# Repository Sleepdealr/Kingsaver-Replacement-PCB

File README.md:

# Kingsaver Replacement PCB

Replacement PCB for the Kingsaver

This has been prototyped and is confirmed working

<br />This work is licensed under a <a rel="license" href="http://creativecommons.org/licenses/by-nc-sa/4.0/">Creative Commons Attribution-NonCommercial-ShareAlike 4.0 Unported License</a>.

# Production

Production gerbers are zipped in the `Gerbers` folder, with JLC assembly files in the `jlcpcb/assembly` folder

You can get USB connectors off LCSC at <https://lcsc.com/product-detail/USB-Connectors_Jing-Extension-of-the-Electronic-Co-920-462A2021D10102_C46398.html>

Photo of proto:

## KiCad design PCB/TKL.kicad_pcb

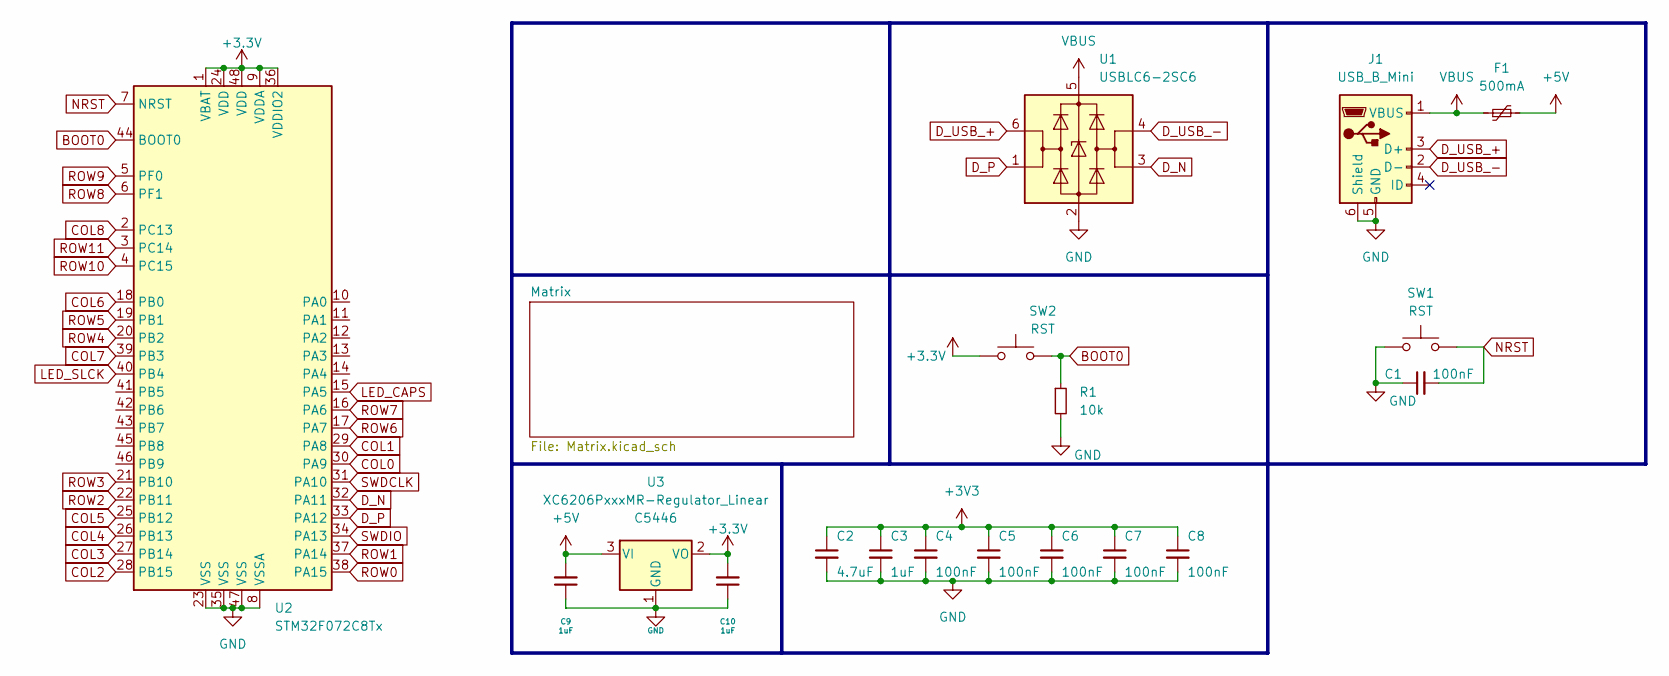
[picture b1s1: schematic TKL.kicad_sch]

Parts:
C1, C4, C5, C6, C7, C8: 100nF; C_0402_1005Metric; LCSC C307331
C2: 4.7uF; C_0402_1005Metric; LCSC C52923
C3, C9, C10: 1uF; C_0402_1005Metric; LCSC C52923
F1: 500mA; Fuse_1206_3216Metric
J1: USB_B_Mini; USB-Mini-B_ LCSC-C46398; LCSC C105424
R1: 10k; R_0402_1005Metric
SW1, SW2: RST; SW_SPST_SKQG_WithoutStem
U1: USBLC6-2SC6; SOT-23-6
U2: STM32F072C8Tx; LQFP-48_7x7mm_P0.5mm
U3: XC6206PxxxMR-Regulator_Linear; SOT-23; LCSC C5446

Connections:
+5V: C9.2, F1.2, U3.3 (VI)
BOOT0: R1.1, SW2.2, U2.44 (BOOT0)
COL0: U2.30 (PA9); also elsewhere on the board
COL1: U2.29 (PA8); also elsewhere on the board
COL2: U2.28 (PB15); also elsewhere on the board
COL3: U2.27 (PB14); also elsewhere on the board
COL4: U2.26 (PB13); also elsewhere on the board
COL5: U2.25 (PB12); also elsewhere on the board
COL6: U2.18 (PB0); also elsewhere on the board
COL7: U2.39 (PB3); also elsewhere on the board
COL8: U2.2 (PC13); also elsewhere on the board
D_N: U1.3 (I/O2), U2.32 (PA11)
D_P: U1.1 (I/O1), U2.33 (PA12)
D_USB_+: J1.3 (D+), U1.6 (I/O1)
D_USB_-: J1.2 (D-), U1.4 (I/O2)
GND: C1.1, C2.2, C3.2, C4.2, C5.2, C6.2, C7.2, C8.2, C9.1, C10.1, J1.5 (GND), J1.6 (Shield), R1.2, SW1.1, U1.2 (GND), U2.8 (VSSA), U2.23 (VSS), U2.35 (VSS), U2.47 (VSS), U3.1 (GND); also elsewhere on the board
LED_CAPS: U2.15 (PA5); also elsewhere on the board
LED_SLCK: U2.40 (PB4); also elsewhere on the board
NRST: C1.2, SW1.2, U2.7 (NRST)
ROW0: U2.38 (PA15); also elsewhere on the board
ROW1: U2.37 (PA14); also elsewhere on the board
ROW2: U2.22 (PB11); also elsewhere on the board
ROW3: U2.21 (PB10); also elsewhere on the board
ROW4: U2.20 (PB2); also elsewhere on the board
ROW5: U2.19 (PB1); also elsewhere on the board
ROW6: U2.17 (PA7); also elsewhere on the board
ROW7: U2.16 (PA6); also elsewhere on the board
ROW8: U2.6 (PF1); also elsewhere on the board
ROW9: U2.5 (PF0); also elsewhere on the board
ROW10: U2.4 (PC15); also elsewhere on the board
ROW11: U2.3 (PC14); also elsewhere on the board
SWDCLK: U2.31 (PA10)
SWDIO: U2.34 (PA13)
VBUS: F1.1, J1.1 (VBUS), U1.5 (VBUS)

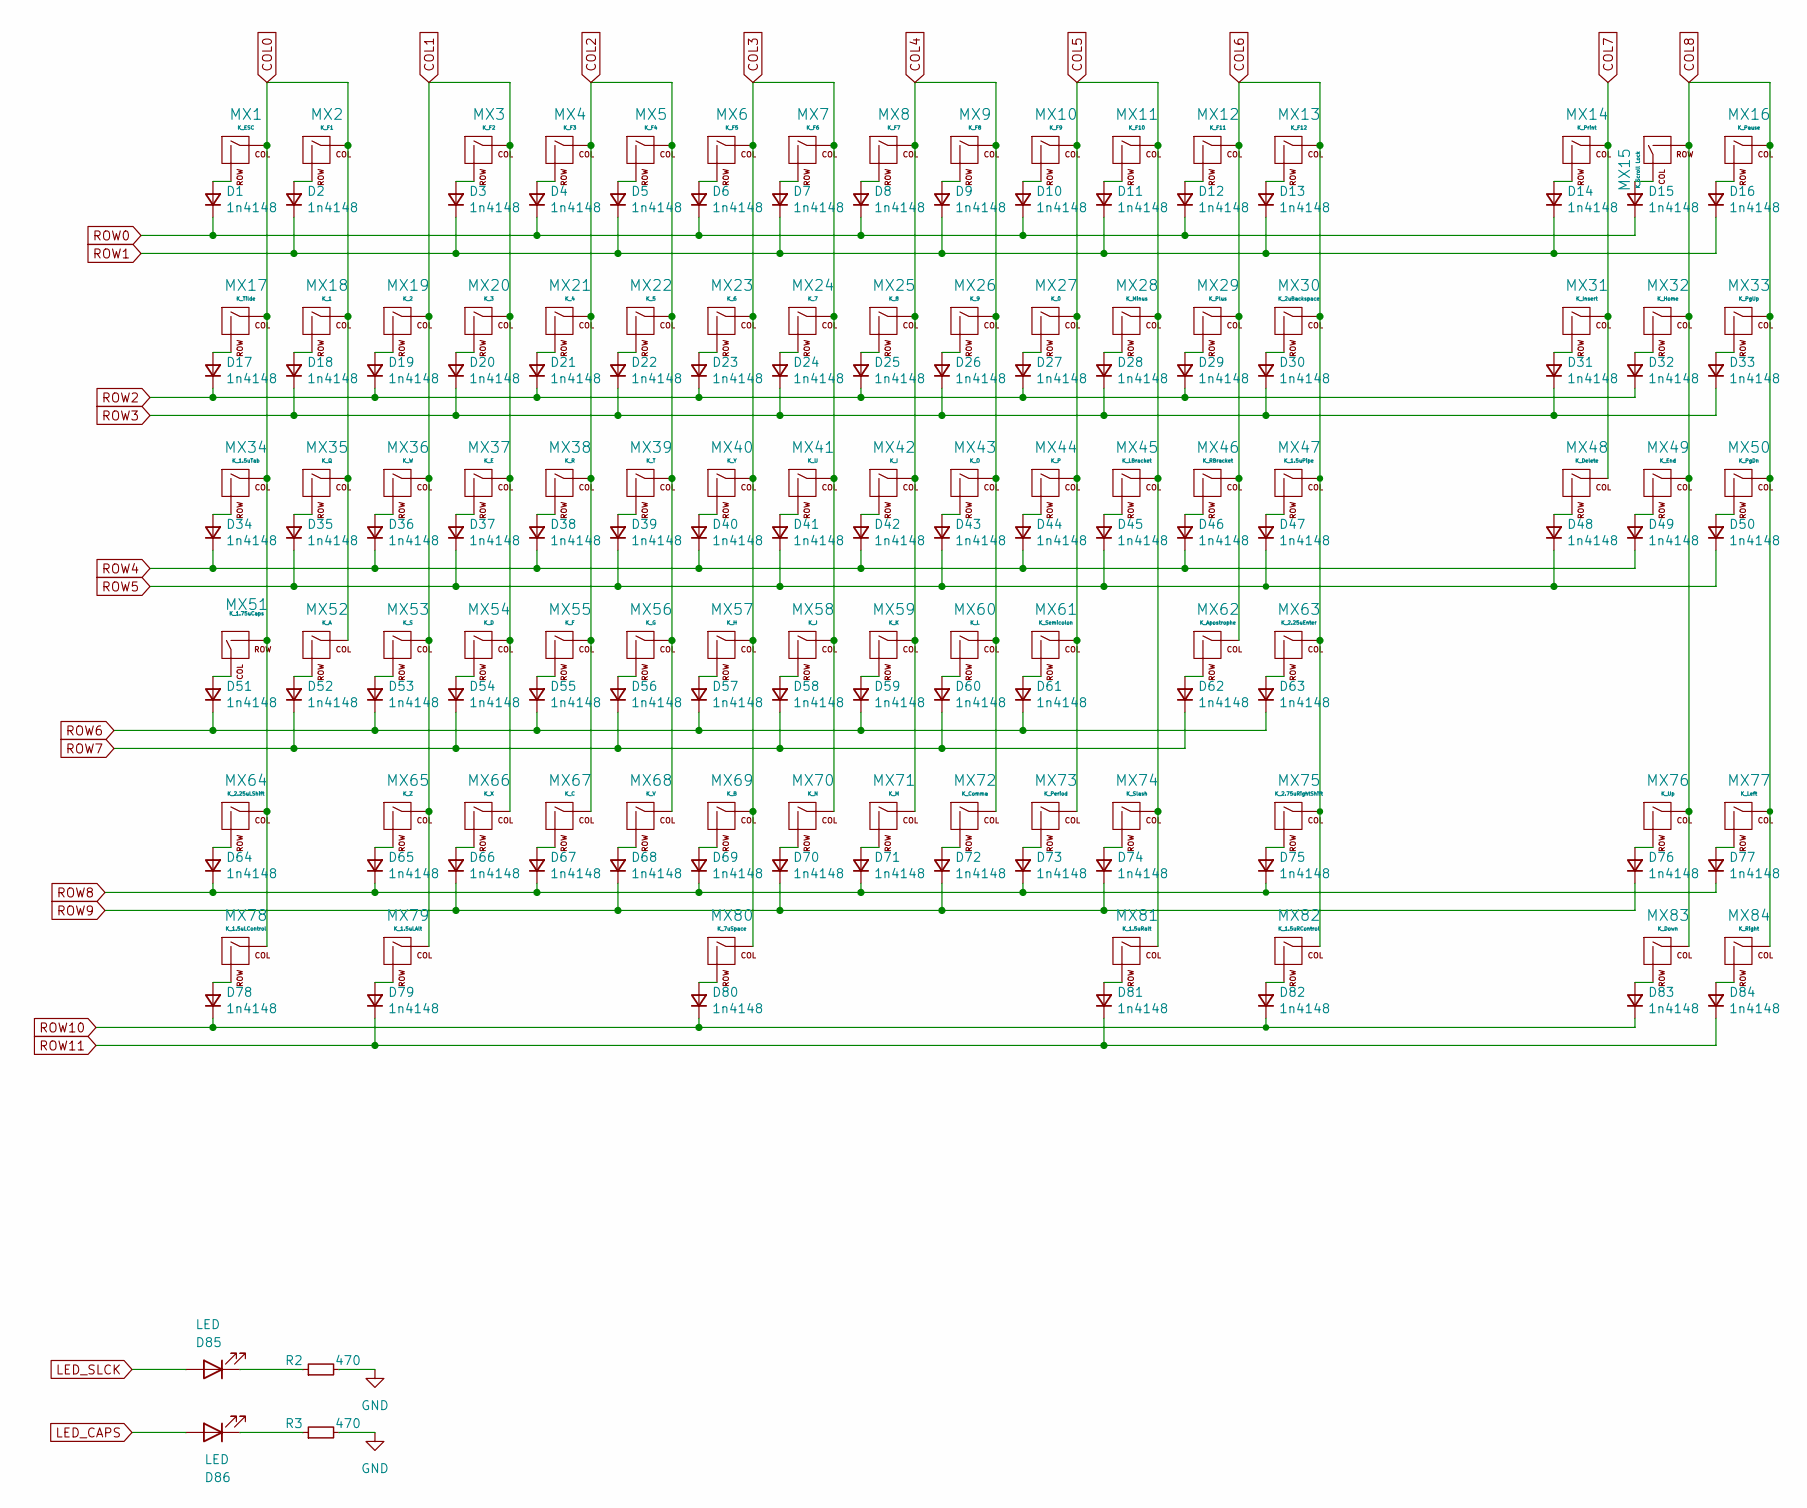
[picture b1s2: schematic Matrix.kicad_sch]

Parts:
D1, D2, D3, D4, D5, D6, D7, D8, D9, D10, D11, D12, D13, D14, D15, D16, D17, D18, D19, D20, D21, D22, D23, D24, D25, D26, D27, D28, D29, D30, D31, D32, D33, D34, D35, D36, D37, D38, D39, D40, D41, D42, D43, D44, D45, D46, D47, D48, D49, D50, D51, D52, D53, D54, D55, D56, D57, D58, D59, D60, D61, D62, D63, D64, D65, D66, D67, D68, D69, D70, D71, D72, D73, D74, D75, D76, D77, D78, D79, D80, D81, D82, D83, D84: 1n4148; D_SOD-123-EditSkilk; LCSC C81598
D85, D86: LED; ALPS-LEDONLY
MX1: K_ESC; SW_Alps_1u
MX2: K_F1; SW_Alps_1u
MX3: K_F2; SW_Alps_1u
MX4: K_F3; SW_Alps_1u
MX5: K_F4; SW_Alps_1u
MX6: K_F5; SW_Alps_1u
MX7: K_F6; SW_Alps_1u
MX8: K_F7; SW_Alps_1u
MX9: K_F8; SW_Alps_1u
MX10: K_F9; SW_Alps_1u
MX11: K_F10; SW_Alps_1u
MX12: K_F11; SW_Alps_1u
MX13: K_F12; SW_Alps_1u
MX14: K_Print; SW_Alps_1u
MX15: K_Scroll Lock; SW_Alps_1u
MX16: K_Pause; SW_Alps_1u
MX17: K_Tilde; SW_Alps_1u
MX18: K_1; SW_Alps_1u
MX19: K_2; SW_Alps_1u
MX20: K_3; SW_Alps_1u
MX21: K_4; SW_Alps_1u
MX22: K_5; SW_Alps_1u
MX23: K_6; SW_Alps_1u
MX24: K_7; SW_Alps_1u
MX25: K_8; SW_Alps_1u
MX26: K_9; SW_Alps_1u
MX27: K_0; SW_Alps_1u
MX28: K_Minus; SW_Alps_1u
MX29: K_Plus; SW_Alps_1u
MX30: K_2uBackspace; SW_Alps_1u
MX31: K_Insert; SW_Alps_1u
MX32: K_Home; SW_Alps_1u
MX33: K_PgUp; SW_Alps_1u
MX34: K_1.5uTab; SW_Alps_1.5u
MX35: K_Q; SW_Alps_1u
MX36: K_W; SW_Alps_1u
MX37: K_E; SW_Alps_1u
MX38: K_R; SW_Alps_1u
MX39: K_T; SW_Alps_1u
MX40: K_Y; SW_Alps_1u
MX41: K_U; SW_Alps_1u
MX42: K_I; SW_Alps_1u
MX43: K_O; SW_Alps_1u
MX44: K_P; SW_Alps_1u
MX45: K_LBracket; SW_Alps_1u
MX46: K_RBracket; SW_Alps_1u
MX47: K_1.5uPipe; SW_Alps_1.75u
MX48: K_Delete; SW_Alps_1u
MX49: K_End; SW_Alps_1u
MX50: K_PgDn; SW_Alps_1u
MX51: K_1.75uCaps; SW_Alps_1.75u
MX52: K_A; SW_Alps_1u
MX53: K_S; SW_Alps_1u
MX54: K_D; SW_Alps_1u
MX55: K_F; SW_Alps_1u
MX56: K_G; SW_Alps_1u
MX57: K_H; SW_Alps_1u
MX58: K_J; SW_Alps_1u
MX59: K_K; SW_Alps_1u
MX60: K_L; SW_Alps_1u
MX61: K_Semicolon; SW_Alps_1u
MX62: K_Apostrophe; SW_Alps_1u
MX63: K_2.25uEnter; SW_Alps_1u
MX64: K_2.25uLShift; SW_Alps_1u
MX65: K_Z; SW_Alps_1u
MX66: K_X; SW_Alps_1u
MX67: K_C; SW_Alps_1u
MX68: K_V; SW_Alps_1u
MX69: K_B; SW_Alps_1u
MX70: K_N; SW_Alps_1u
MX71: K_M; SW_Alps_1u
MX72: K_Comma; SW_Alps_1u
MX73: K_Period; SW_Alps_1u
MX74: K_Slash; SW_Alps_1u
MX75: K_2.75uRightShift; SW_Alps_1u
MX76: K_Up; SW_Alps_1u
MX77: K_Left; SW_Alps_1u
MX78: K_1.5uLControl; SW_Alps_1.5u
MX79: K_1.5uLAlt; SW_Alps_1.5u
MX80: K_7uSpace; SW_Alps_1u
MX81: K_1.5uRalt; SW_Alps_1.5u
MX82: K_1.5uRControl; SW_Alps_1.5u
MX83: K_Down; SW_Alps_1u
MX84: K_Right; SW_Alps_1u
R2, R3: 470; R_0402_1005Metric

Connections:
COL0: MX1.1 (COL), MX2.1 (COL), MX17.1 (COL), MX18.1 (COL), MX34.1 (COL), MX35.1 (COL), MX51.2 (ROW), MX52.1 (COL), MX64.1 (COL), MX78.1 (COL); also elsewhere on the board
COL1: MX3.1 (COL), MX19.1 (COL), MX20.1 (COL), MX36.1 (COL), MX37.1 (COL), MX53.1 (COL), MX54.1 (COL), MX65.1 (COL), MX66.1 (COL), MX79.1 (COL); also elsewhere on the board
COL2: MX4.1 (COL), MX5.1 (COL), MX21.1 (COL), MX22.1 (COL), MX38.1 (COL), MX39.1 (COL), MX55.1 (COL), MX56.1 (COL), MX67.1 (COL), MX68.1 (COL); also elsewhere on the board
COL3: MX6.1 (COL), MX7.1 (COL), MX23.1 (COL), MX24.1 (COL), MX40.1 (COL), MX41.1 (COL), MX57.1 (COL), MX58.1 (COL), MX69.1 (COL), MX70.1 (COL), MX80.1 (COL); also elsewhere on the board
COL4: MX8.1 (COL), MX9.1 (COL), MX25.1 (COL), MX26.1 (COL), MX42.1 (COL), MX43.1 (COL), MX59.1 (COL), MX60.1 (COL), MX71.1 (COL), MX72.1 (COL); also elsewhere on the board
COL5: MX10.1 (COL), MX11.1 (COL), MX27.1 (COL), MX28.1 (COL), MX44.1 (COL), MX45.1 (COL), MX61.1 (COL), MX73.1 (COL), MX74.1 (COL), MX81.1 (COL); also elsewhere on the board
COL6: MX12.1 (COL), MX13.1 (COL), MX29.1 (COL), MX30.1 (COL), MX46.1 (COL), MX47.1 (COL), MX62.1 (COL), MX63.1 (COL), MX75.1 (COL), MX82.1 (COL); also elsewhere on the board
COL7: MX14.1 (COL), MX31.1 (COL), MX48.1 (COL); also elsewhere on the board
COL8: MX15.2 (ROW), MX16.1 (COL), MX32.1 (COL), MX33.1 (COL), MX49.1 (COL), MX50.1 (COL), MX76.1 (COL), MX77.1 (COL), MX83.1 (COL), MX84.1 (COL); also elsewhere on the board
GND: R2.2, R3.2; also elsewhere on the board
LED_CAPS: D86.2 (A); also elsewhere on the board
LED_SLCK: D85.2 (A); also elsewhere on the board
unnamed: D1.2 (A), MX1.2 (ROW)
unnamed: D2.2 (A), MX2.2 (ROW)
unnamed: D3.2 (A), MX3.2 (ROW)
unnamed: D4.2 (A), MX4.2 (ROW)
unnamed: D5.2 (A), MX5.2 (ROW)
unnamed: D6.2 (A), MX6.2 (ROW)
unnamed: D7.2 (A), MX7.2 (ROW)
unnamed: D8.2 (A), MX8.2 (ROW)
unnamed: D9.2 (A), MX9.2 (ROW)
unnamed: D10.2 (A), MX10.2 (ROW)
unnamed: D11.2 (A), MX11.2 (ROW)
unnamed: D12.2 (A), MX12.2 (ROW)
unnamed: D13.2 (A), MX13.2 (ROW)
unnamed: D14.2 (A), MX14.2 (ROW)
unnamed: D15.2 (A), MX15.1 (COL)
unnamed: D16.2 (A), MX16.2 (ROW)
unnamed: D17.2 (A), MX17.2 (ROW)
unnamed: D18.2 (A), MX18.2 (ROW)
unnamed: D19.2 (A), MX19.2 (ROW)
unnamed: D20.2 (A), MX20.2 (ROW)
unnamed: D21.2 (A), MX21.2 (ROW)
unnamed: D22.2 (A), MX22.2 (ROW)
unnamed: D23.2 (A), MX23.2 (ROW)
unnamed: D24.2 (A), MX24.2 (ROW)
unnamed: D25.2 (A), MX25.2 (ROW)
unnamed: D26.2 (A), MX26.2 (ROW)
unnamed: D27.2 (A), MX27.2 (ROW)
unnamed: D28.2 (A), MX28.2 (ROW)
unnamed: D29.2 (A), MX29.2 (ROW)
unnamed: D30.2 (A), MX30.2 (ROW)
unnamed: D31.2 (A), MX31.2 (ROW)
unnamed: D32.2 (A), MX32.2 (ROW)
unnamed: D33.2 (A), MX33.2 (ROW)
unnamed: D34.2 (A), MX34.2 (ROW)
unnamed: D35.2 (A), MX35.2 (ROW)
unnamed: D36.2 (A), MX36.2 (ROW)
unnamed: D37.2 (A), MX37.2 (ROW)
unnamed: D38.2 (A), MX38.2 (ROW)
unnamed: D39.2 (A), MX39.2 (ROW)
unnamed: D40.2 (A), MX40.2 (ROW)
unnamed: D41.2 (A), MX41.2 (ROW)
unnamed: D42.2 (A), MX42.2 (ROW)
unnamed: D43.2 (A), MX43.2 (ROW)
unnamed: D44.2 (A), MX44.2 (ROW)
unnamed: D45.2 (A), MX45.2 (ROW)
unnamed: D46.2 (A), MX46.2 (ROW)
unnamed: D47.2 (A), MX47.2 (ROW)
unnamed: D48.2 (A), MX48.2 (ROW)
unnamed: D49.2 (A), MX49.2 (ROW)
unnamed: D50.2 (A), MX50.2 (ROW)
unnamed: D51.2 (A), MX51.1 (COL)
unnamed: D52.2 (A), MX52.2 (ROW)
unnamed: D53.2 (A), MX53.2 (ROW)
unnamed: D54.2 (A), MX54.2 (ROW)
unnamed: D55.2 (A), MX55.2 (ROW)
unnamed: D56.2 (A), MX56.2 (ROW)
unnamed: D57.2 (A), MX57.2 (ROW)
unnamed: D58.2 (A), MX58.2 (ROW)
unnamed: D59.2 (A), MX59.2 (ROW)
unnamed: D60.2 (A), MX60.2 (ROW)
unnamed: D61.2 (A), MX61.2 (ROW)
unnamed: D62.2 (A), MX62.2 (ROW)
unnamed: D63.2 (A), MX63.2 (ROW)
unnamed: D64.2 (A), MX64.2 (ROW)
unnamed: D65.2 (A), MX65.2 (ROW)
unnamed: D66.2 (A), MX66.2 (ROW)
unnamed: D67.2 (A), MX67.2 (ROW)
unnamed: D68.2 (A), MX68.2 (ROW)
unnamed: D69.2 (A), MX69.2 (ROW)
unnamed: D70.2 (A), MX70.2 (ROW)
unnamed: D71.2 (A), MX71.2 (ROW)
unnamed: D72.2 (A), MX72.2 (ROW)
unnamed: D73.2 (A), MX73.2 (ROW)
unnamed: D74.2 (A), MX74.2 (ROW)
unnamed: D75.2 (A), MX75.2 (ROW)
unnamed: D76.2 (A), MX76.2 (ROW)
unnamed: D77.2 (A), MX77.2 (ROW)
unnamed: D78.2 (A), MX78.2 (ROW)
unnamed: D79.2 (A), MX79.2 (ROW)
unnamed: D80.2 (A), MX80.2 (ROW)
unnamed: D81.2 (A), MX81.2 (ROW)
unnamed: D82.2 (A), MX82.2 (ROW)
unnamed: D83.2 (A), MX83.2 (ROW)
unnamed: D84.2 (A), MX84.2 (ROW)
unnamed: D85.1 (K), R2.1
unnamed: D86.1 (K), R3.1
ROW0: D1.1 (K), D4.1 (K), D6.1 (K), D8.1 (K), D10.1 (K), D12.1 (K), D15.1 (K); also elsewhere on the board
ROW1: D2.1 (K), D3.1 (K), D5.1 (K), D7.1 (K), D9.1 (K), D11.1 (K), D13.1 (K), D14.1 (K), D16.1 (K); also elsewhere on the board
ROW2: D17.1 (K), D19.1 (K), D21.1 (K), D23.1 (K), D25.1 (K), D27.1 (K), D29.1 (K), D32.1 (K); also elsewhere on the board
ROW3: D18.1 (K), D20.1 (K), D22.1 (K), D24.1 (K), D26.1 (K), D28.1 (K), D30.1 (K), D31.1 (K), D33.1 (K); also elsewhere on the board
ROW4: D34.1 (K), D36.1 (K), D38.1 (K), D40.1 (K), D42.1 (K), D44.1 (K), D46.1 (K), D49.1 (K); also elsewhere on the board
ROW5: D35.1 (K), D37.1 (K), D39.1 (K), D41.1 (K), D43.1 (K), D45.1 (K), D47.1 (K), D48.1 (K), D50.1 (K); also elsewhere on the board
ROW6: D51.1 (K), D53.1 (K), D55.1 (K), D57.1 (K), D59.1 (K), D61.1 (K), D63.1 (K); also elsewhere on the board
ROW7: D52.1 (K), D54.1 (K), D56.1 (K), D58.1 (K), D60.1 (K), D62.1 (K); also elsewhere on the board
ROW8: D64.1 (K), D65.1 (K), D67.1 (K), D69.1 (K), D71.1 (K), D73.1 (K), D75.1 (K), D77.1 (K); also elsewhere on the board
ROW9: D66.1 (K), D68.1 (K), D70.1 (K), D72.1 (K), D74.1 (K), D76.1 (K); also elsewhere on the board
ROW10: D78.1 (K), D80.1 (K), D82.1 (K), D83.1 (K); also elsewhere on the board
ROW11: D79.1 (K), D81.1 (K), D84.1 (K); also elsewhere on the board

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
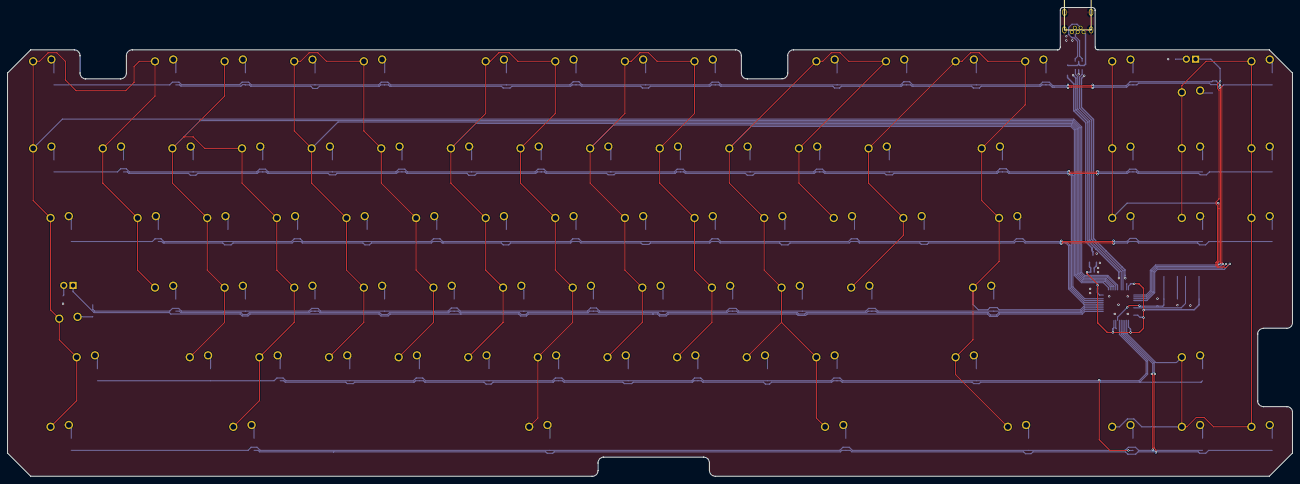
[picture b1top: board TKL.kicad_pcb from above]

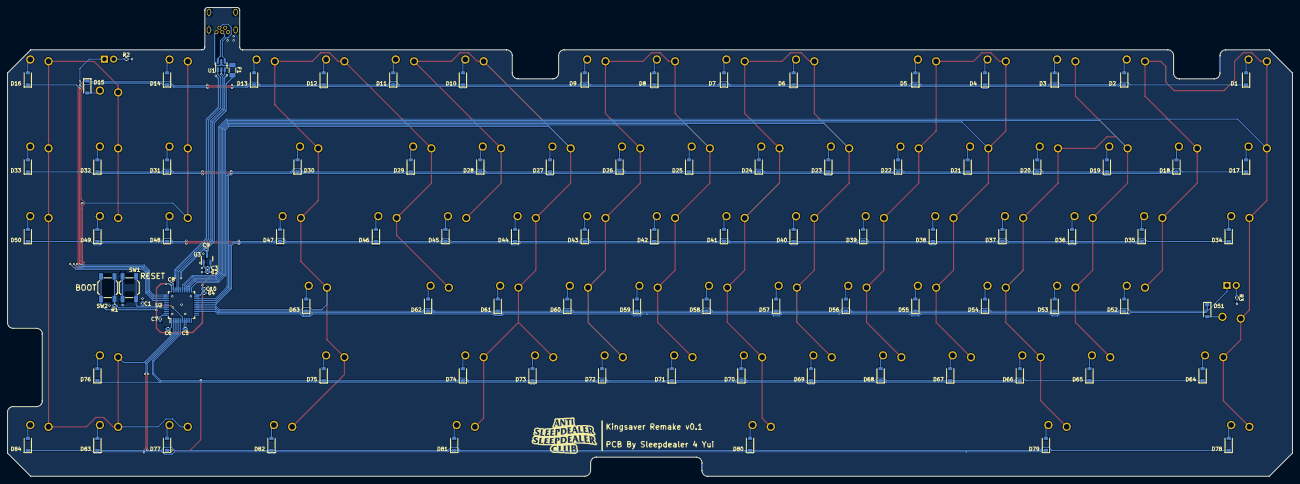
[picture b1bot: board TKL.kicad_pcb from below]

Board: 2 copper layers, 351.6 x 128.3 mm, 191 parts (104 on the bottom side), 119 nets.

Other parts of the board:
H1: MountingHole; assc_fixed

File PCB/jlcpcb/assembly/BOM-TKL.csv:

Comment,Designator,Footprint,LCSC
470,"R2,R3",R_0402_1005Metric,C25117
10k,R1,R_0402_1005Metric,C25744
USBLC6-2SC6,U1,SOT-23-6,C2827654
100nF,"C1,C4,C5,C6,C7,C8",C_0402_1005Metric,C307331
RST,"SW1,SW2",SW_SPST_SKQG_WithoutStem,C318884
1uF,"C10,C2,C3,C9",C_0402_1005Metric,C52923
XC6206PxxxMR-Regulator_Linear,U3,SOT-23,C5446
500mA,F1,Fuse_1206_3216Metric,C70076
STM32F072C8Tx,U2,LQFP-48_7x7mm_P0.5mm,C80488
1n4148,"D1,D10,D11,D12,D13,D14,D15,D16,D17,D18,D19,D2,D20,D21,D22,D23,D24,D25,D26,D27,D28,D29,D3,D30,D31,D32,D33,D34,D35,D36,D37,D38,D39,D4,D40,D41,D42,D43,D44,D45,D46,D47,D48,D49,D5,D50,D51,D52,D53,D54,D55,D56,D57,D58,D59,D6,D60,D61,D62,D63,D64,D65,D66,D67,D68,D69,D7,D70,D71,D72,D73,D74,D75,D76,D77,D78,D79,D8,D80,D81,D82,D83,D84,D9",D_SOD-123-EditSkilk,C81598

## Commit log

2023-01-22 Init to winit
2023-01-22 Add license
